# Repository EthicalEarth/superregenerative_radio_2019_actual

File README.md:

# superregenerative radio

Super-regenerative radio for receiving signals in the range of 20 meters. The circuit board has been reduced, which can increase the maximum operating frequency.

A rather loud reception of stations of distant stations was noted when using an amplifier on a TDA2030A chip.

The frequency range depends on the specifically installed components that were measured during operation. The coil was used with 6-15 turns on a diameter of 10 mm, and the capacitor used a standard 40-240 picofarad.

Using a converter on a chip, it was possible to receive an FM station of 80-108 MHz, although the quality of such a reception is naturally lower.

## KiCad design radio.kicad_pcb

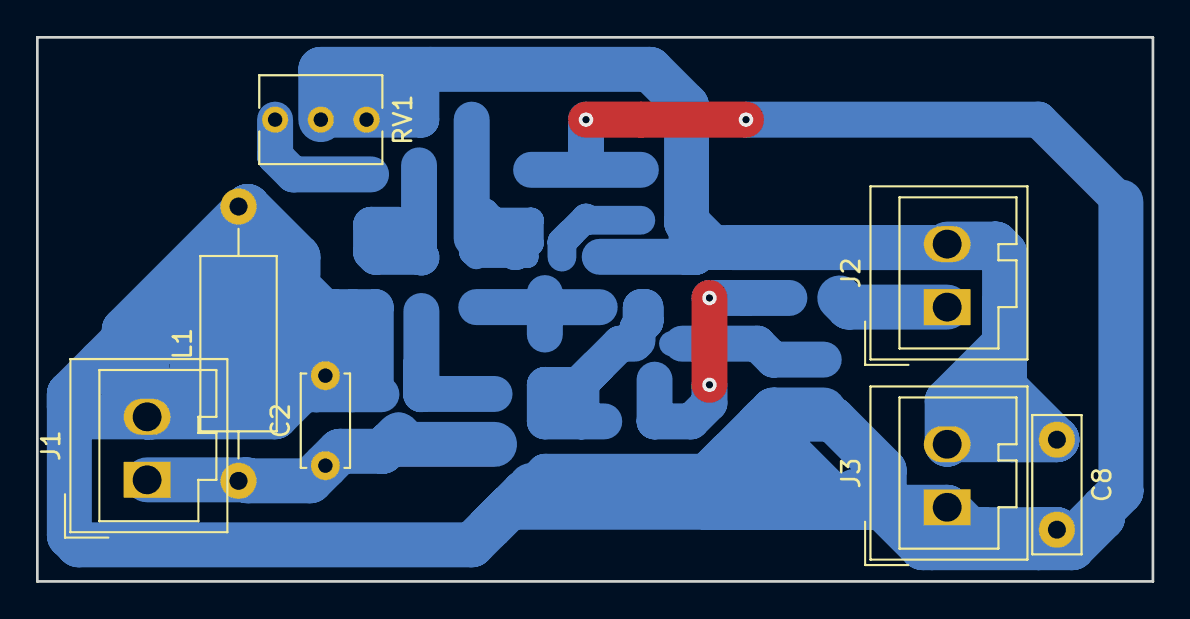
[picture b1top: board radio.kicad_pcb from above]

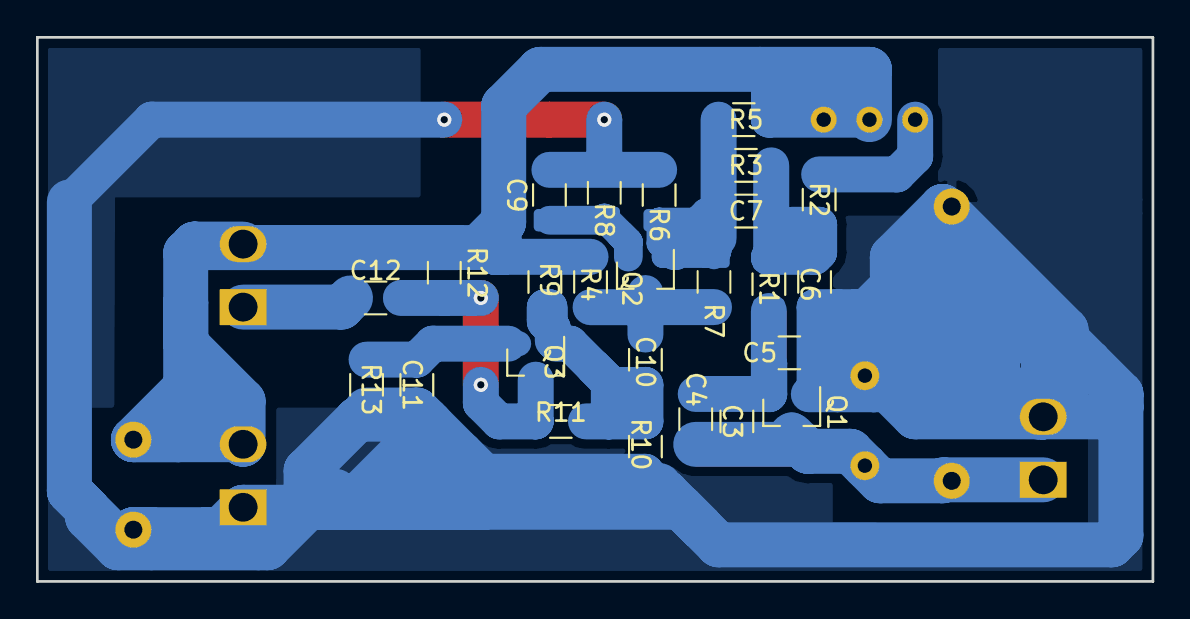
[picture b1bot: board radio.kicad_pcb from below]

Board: 2 copper layers, 62.0 x 30.2 mm, 32 parts (25 on the bottom side), 13 nets.

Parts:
C2: 2-7pF; C_Disc_D5.0mm_W2.5mm_P5.00mm
C3, C4: 12-300pF; C_1206_3216Metric
C5: 300pF; C_1206_3216Metric
C6, C9, C11: 0.05uF; C_1206_3216Metric
C7: C; C_1206_3216Metric
C8: 100uF; C_Disc_D7.5mm_W2.5mm_P5.00mm
C10, C12: 0.1; C_1206_3216Metric
J1, J2, J3: Conn_01x02_Male; Wago_734-132_1x02_P3.50mm_Vertical
L1: L; L_Axial_L9.5mm_D4.0mm_P15.24mm_Horizontal_Fastron_SMCC
Q1: BC807; SOT-23
Q2, Q3: BC817; SOT-23
R1: 1k; R_1206_3216Metric_Pad1.42x1.75mm_HandSolder
R2, R6, R8, R10, R13: 1.8k; R_1206_3216Metric
R3: 47k; R_1206_3216Metric
R4, R5, R7, R9, R11, R12: 15k; R_1206_3216Metric
RV1: 6.8k; Potentiometer_Vishay_T73XW_Horizontal

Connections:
GND: C2.2, C5.2, C6.2, C8.2, C9.2, C11.2, J1.2, J3.1, L1.2, Q1.1, R6.2, R8.2, R10.2, R13.2
unnamed: C2.1, C3.2, C4.2, J1.1, L1.1, Q1.3
unnamed: C3.1, C4.1, C5.1, Q1.2, R1.2
unnamed: C6.1, C7.2, R1.1, R2.2, R3.2
unnamed: C7.1, Q2.1, R3.1, R5.2, R6.1, R7.2
unnamed: C8.1, J2.2, J3.2, R4.1, R5.1, R9.1, R12.1, RV1.1, RV1.2
unnamed: C9.1, Q2.2, R8.1
unnamed: C10.1, Q3.1, R9.2, R10.1, R11.2
unnamed: C10.2, Q2.3, R4.2, R7.1
unnamed: C11.1, Q3.2, R13.1
unnamed: C12.1, J2.1
unnamed: C12.2, Q3.3, R11.1, R12.2
unnamed: R2.1, RV1.3
